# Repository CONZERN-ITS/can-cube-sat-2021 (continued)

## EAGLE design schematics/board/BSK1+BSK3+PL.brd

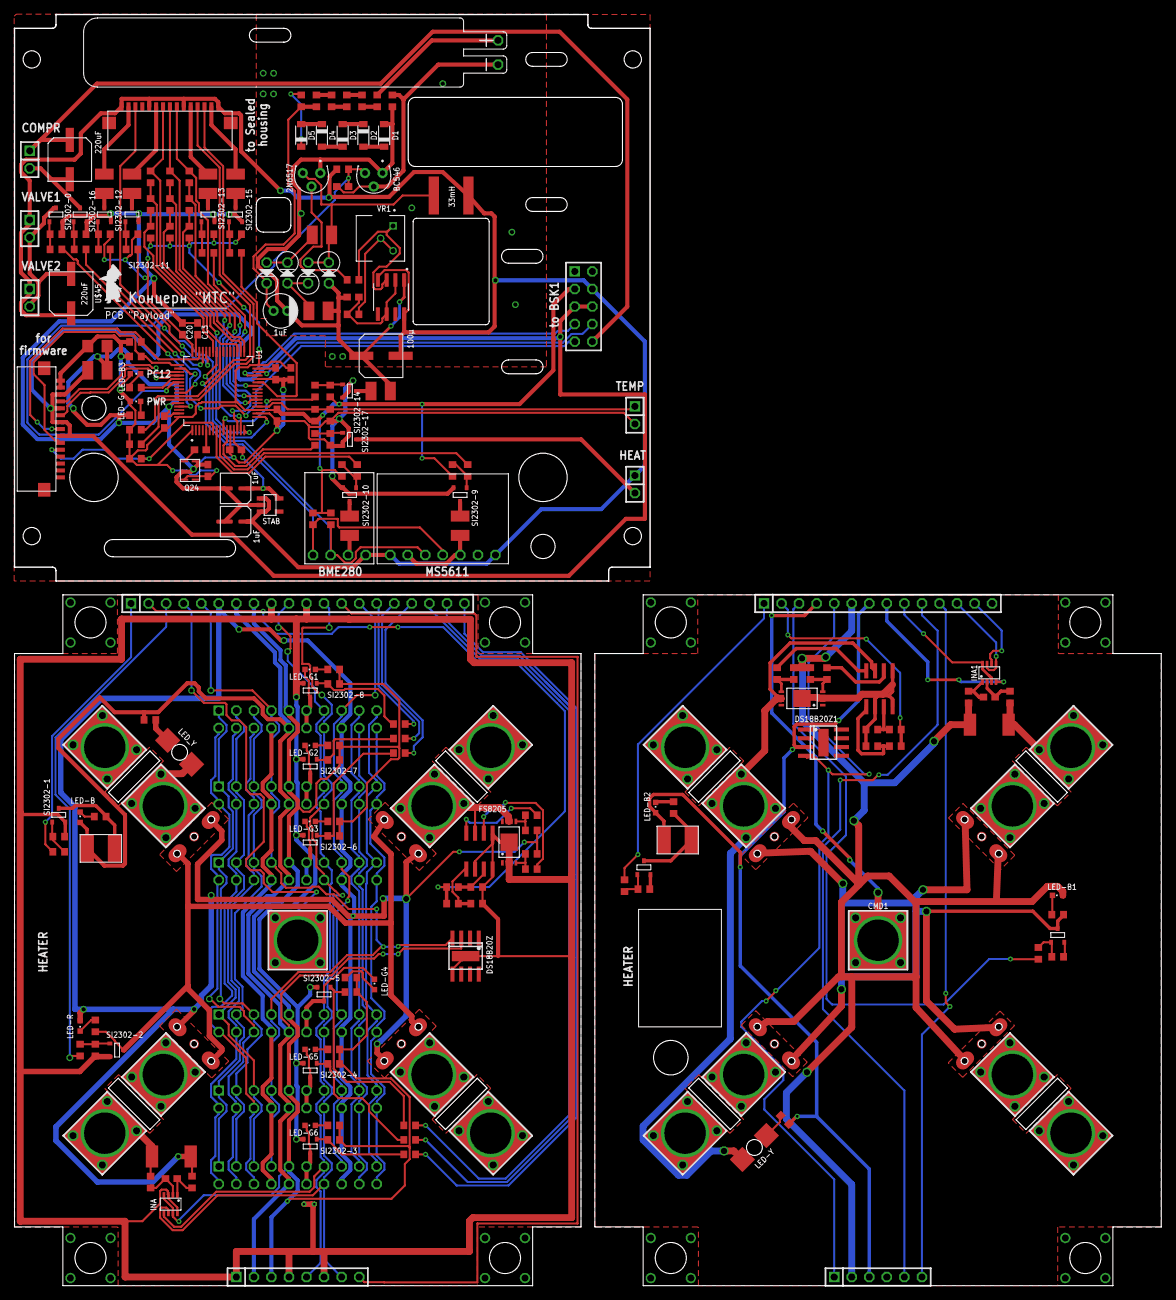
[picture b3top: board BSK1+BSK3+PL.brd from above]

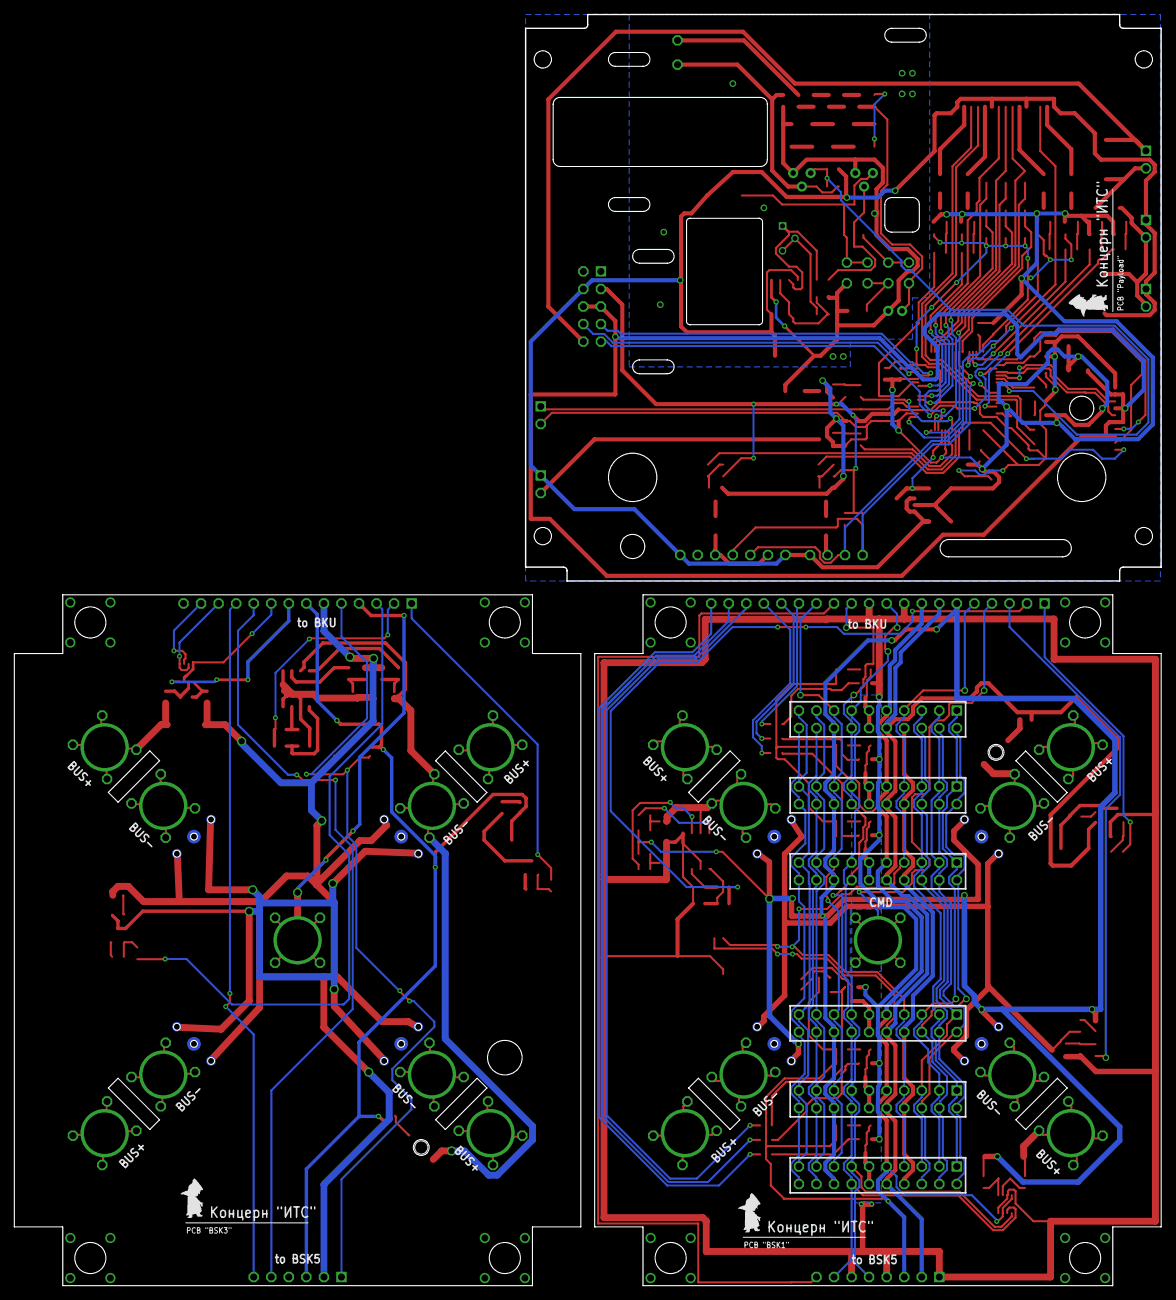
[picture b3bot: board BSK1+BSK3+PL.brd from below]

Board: 2 copper layers, 166.0 x 184.0 mm, 246 parts (9 on the bottom side), 200 nets.

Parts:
2N6517: DS1820; TO92/TO226
BC546: DS1820; TO92/TO226
BKU: 1X20
BKU1: 1X14
BME280: BME280BME280-PINS-ONLY; BME280-PINS-ONLY
BSK1: 1X06
BSK2: 2X05
BSK5: 1X08
C1, C41: 0,1µ; C0603
C2, C3, C4, C6, C18, C20: 100nF; C0603
C5, C7: 22nF; C1210
C8: 1nF; C0603
C9, C13: 2,2µ; C0603
C10: 10nF; C0603
C11: 100pF; C0603
C12, C14: 1uF; ECAP-SMD-D4
C19: 10µ; C1206
CMD, CMD1: KCONNECTQUAD; KCONNECT_QUAD
COMPR: 1X02
D1, D2, D3, D4, D5: DIODE-MBR; SOD123
DS18B20Z, DS18B20Z1: DS18B20Z; SOIC8+HEAT_S
FS8205: FS8205A+
HEAT: 1X02
INA, INA1: INA219AID; SOT23-8
JP1, JP2, JP3, JP4, JP5, JP6: 2X10
LED-B, LED-B1, LED-B2, LED-B3: CHIPLED_0603
LED-G, LED-G1, LED-G2, LED-G3, LED-G4, LED-G5, LED-G6: CHIPLED_0603
LED-R: CHIPLED_0603
LED-Y: LAP4-BOTTOM; P47F-BOTTOM
LED_Y: LAP4-BOTTOM; P47F-BOTTOM
MS5611: MS5611MS5611-PIN-ONLY; MS5611-PINS-ONLY
Q24: Q24
R1, R2, R94, R95: 200k; R0603
R3, R5, R26, R27, R28, R29, R30, R31, R32, R33, R34, R35, R48, R49, R59, R61, R64, R66, R69, R72, R101, R104, R106, R108: 100R; R0603
R4, R7, R36, R37, R87: 100k; R0603
R6, R8, R9, R12, R13, R14, R18, R20, R40, R42, R58, R60, R63, R65, R68, R71, R82, R83, R84, R85, R86, R100, R103, R105, R107: 1M; R0603
R10, R11, R15, R16, R17, R21, R22, R23, R38, R39, R51, R54: 2k; R0603
R19, R88: 3k3; R0603
R24, R25, R46, R47: 2k26; R0603
R41: 1k5; R0603
R43, R75: R01; R2512
R44, R45, R76, R77: 10R; R0603
R50, R52, R53, R89, R90, R91, R92, R93, R96, R97, R98, R99: 10k; R0603
R55, R56, R111, R112: 5k1; R0603
R57, R62, R67, R70, R73, R74, R102: 0.05A; R1210
R78: 0.5A; R1210
R79: 1k; R0603
R80: 4k7; R0603
R81, R110: 22k; R0603
R109: 124k; R0603
SI2302-0, SI2302-1, SI2302-2, SI2302-3, SI2302-4, SI2302-5, SI2302-6, SI2302-7, SI2302-8, SI2302-9, SI2302-10, SI2302-11, SI2302-12, SI2302-13, SI2302-14, SI2302-15, SI2302-16, SI2302-17: SI2302CDS; SOT23-3
STAB: ADP150AUJZ-3.3-R7; SOT23-5
TEMP: 1X02
U1: STM32F405RGT6; QFP50P1200X1200X160-64N
U2: LMC555; SOIC127P599X175-8N
U$1, U$2, U$3, U$4, U$5, U$6, U$7, U$8, U$9, U$10, U$11, U$12, U$18, U$19, U$20, U$21: KCONNECT
U$13: FS8205A+
U$14, U$22: MOCD; SOIC8
U$15, U$17: SI2302CDS; SOT23-3
U$16, U$24: EM_HEAT
U$23, U$25, U$27, U$28, U$29, U$30, U$31, U$32: GRAFITGRAFIT4_2; GRAFIT4_2
U$26: PCB "BSK1"; ITS-LOGO
U$33: PCB "BSK3"; ITS-LOGO
U$34: 100µ; ECAP100-CMD
U$35, U$36, U$37, U$38: BA159
U$39: 1uF; ECAP1MK
U$40: DOSIM
U$41, U$43: FFC-CONNECT68611; 68611
U$42: 33mH; RCH114NP
U$44, U$45: 220uF; ECAP220-CMD
U$46, U$47: PCB "Payload"; ITS-LOGO
VALVE1, VALVE2: 1X02
VR1: 3362H-1-502LF; TRIM_3362H-1-502LF

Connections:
1: R39.2, U$15.3, U$16.2
1W: BKU.5, DS18B20Z.4, JP1.7, JP2.7, JP3.7, JP4.7, JP5.7, JP6.7
1W1: BKU1.5, BSK1.1, DS18B20Z1.4
2: R41.2, U$17.3, U$23.P$1, U$23.P$4, U$25.P$1, U$25.P$4, U$31.P$1, U$31.P$4, U$32.P$1, U$32.P$4
3: R11.2, SI2302-1.3, U$24.2
3V1: BKU1.8, INA1.4
3V2: BSK2.3, C2.2, C6.2, C10.2, C18.2, C19.2, C20.2, LED-B3.A, LED-G.A, Q24.P$4, R50.2, R52.2, R53.2, R55.1, R56.1, R58.2, R60.2, R63.2, R65.2, R68.2, R71.2, R97.2, R98.2, R99.2, R100.2, R110.2, R111.1, R112.1, U1.1, U1.19, U1.32, U1.48, U1.64, U$43.P$1, U$43.P$2
3V3: BKU.8, BSK5.3, INA.4, INA.7, JP1.9, JP2.9, JP3.9, JP4.9, JP5.9, JP6.9, R6.1, R8.2, R9.1, R12.1, R13.2, R14.1, R15.1, R16.1, R17.1, R21.1, R22.1, R23.1
4: R19.2, SI2302-2.3, U$27.P$1, U$27.P$4, U$28.P$1, U$28.P$4, U$29.P$1, U$29.P$4, U$30.P$1, U$30.P$4
4OXV: R66.1, U1.45
5V: BKU.7, BSK5.2, DS18B20Z.3, JP1.10, JP2.10, JP3.10, JP4.10, JP5.10, JP6.10, LED-B.A, R10.1, U$24.1
5V1: BKU1.7, BSK1.3, DS18B20Z1.3, LED-B2.A, R38.1, U$16.1
5V2: BME280.P$1, BSK2.4, C14.P+, HEAT.1, MS5611.P$1, MS5611.P$7, R88.1, STAB.P$1, STAB.P$3, U2.4, U2.8, U$34.P$2, U$41.P$1, U$41.P$5, U$41.P$10, U$41.P$15, U$42.P$1, U$45.P$1, VALVE1.1, VALVE2.1
B1-CMD: BKU.4, CMD.1, CMD.2, CMD.3, CMD.4, CMD.P$1, CMD.P$2
B1-KHEAT: BKU.1, R32.2
B1-KVCC: BKU.2, R24.2, R25.2
B1-ROZE: BKU.3, R33.2
B3-CMD: BKU1.4, CMD1.1, CMD1.2, CMD1.3, CMD1.4, CMD1.P$1, CMD1.P$2
B3-KHEAT: BKU1.1, R48.2
B3-KVCC: BKU1.2, R46.2, R47.2
B3-ROZE: BKU1.3, R49.2
B5-KHEAT: BKU1.10, BSK1.5
BME280-EXT: R61.1, U1.8
BME280-INT: R101.1, U1.27
BMS1: JP1.1, JP2.1, JP3.1, JP4.5, JP5.3, JP6.3
BMS2: JP1.2, JP2.2, JP3.2, JP4.6, JP5.4, JP6.4
BMS3: JP1.3, JP2.3, JP3.3, JP4.1, JP5.5, JP6.5
BMS4: JP1.4, JP2.4, JP3.4, JP4.2, JP5.6, JP6.6
BMS5: JP1.5, JP2.5, JP3.5, JP4.3, JP5.1, JP6.1
BMS6: JP1.6, JP2.6, JP3.6, JP4.4, JP5.2, JP6.2
BMS+: JP1.8, JP2.8, JP3.8, JP4.8, JP5.8, JP6.8
BUS+: BKU.6, JP1.16, JP2.16, JP3.16, JP4.16, JP5.16, JP6.16, LED-R.A, R4.1, R7.2, R75.2, R76.1, U$27.P$2, U$27.P$5, U$28.P$2, U$28.P$5, U$29.P$2, U$29.P$5, U$30.P$2, U$30.P$5
BUS+1: BKU1.6, BSK1.2, LED-B1.A, R36.1, R37.2, R43.2, R44.1, U$23.P$2, U$23.P$5, U$25.P$2, U$25.P$5, U$31.P$2, U$31.P$5, U$32.P$2, U$32.P$5
BUS+2: BSK2.10, COMPR.1, U$44.P$1
CO: R91.1, U1.16, U$41.P$7
COMPR: R106.1, U1.57
CTRL-CO-1: R91.2, R96.1, U1.35
CTRL-CO-2: R96.2, R97.1, U1.42
CTRL-NH3-1: R90.2, R93.1, U1.33
CTRL-NH3-2: R93.2, R98.1, U1.34
CTRL-NO2-1: R89.2, R92.1, U1.23
CTRL-NO2-2: R92.2, R99.1, U1.22
DOS-G: 2N6517.1, BC546.1, C4.1, C7.2, D1.A, R73.1, R87.2, U2.1, U$34.P$1, U$35.P$1, U$39.P$2
DOSE: BC546.3, C11.2, R88.2, U1.54
DOSIM: R72.1, U1.10
G-4OXV: R67.1, U$41.P$2
G-BME: R102.1, U$41.P$14
G-MICS: R74.1, U$41.P$6
G-MS: R70.1, U$41.P$11
GND: BKU.9, BKU.11, BSK5.1, BSK5.4, BSK5.6, DS18B20Z.5, DS18B20Z.HEAT, FS8205.23, FS8205.HEAT, INA.3, INA.8, R1.1, R2.1, R18.2, R20.2, SI2302-1.2, SI2302-2.2, SI2302-3.2, SI2302-4.2, SI2302-5.2, SI2302-6.2, SI2302-7.2, SI2302-8.2, U$22.2, U$22.4, U$22.5
GND4: BKU1.9, BKU1.14, BSK1.4, DS18B20Z1.5, DS18B20Z1.HEAT, INA1.3, INA1.8, R40.2, R42.2, R94.1, R95.1, U$13.23, U$13.HEAT, U$14.2, U$14.4, U$14.5, U$15.2, U$17.2
GND9: C2.1, C3.2, C6.1, C9.1, C10.1, C12.P-, C13.1, C14.P-, C18.1, C19.1, C20.1, Q24.P$2, R54.1, R78.1, R103.2, R105.2, R107.2, R109.1, SI2302-0.2, SI2302-9.2, SI2302-10.2, SI2302-11.2, SI2302-12.2, SI2302-13.2, SI2302-14.2, SI2302-15.2, SI2302-16.2, SI2302-17.2, STAB.P$2, TEMP.2, U1.12, U1.18, U1.28, U1.60, U1.63
GND-4OXV: R67.2, SI2302-12.3
GND-BME-EXT: R62.2, SI2302-10.3
GND-BME-INT: R102.2, SI2302-15.3
GND-COMPR: COMPR.2, SI2302-16.3, U$44.P$2
GND-DOSIM: R73.2, SI2302-14.3
GND-HEAT: HEAT.2, SI2302-17.3
GND-MICS: R74.2, SI2302-11.3
GND-MS-EXT: R57.2, SI2302-9.3
GND-MS-INT: R70.2, SI2302-13.3
GND-OUT: BSK2.5, BSK2.6, R78.2, U$43.P$3, U$43.P$5, U$43.P$7, U$43.P$9
GND-VALVE: SI2302-0.3, U$45.P$2, VALVE1.2, VALVE2.2
HEAT: R108.1, U1.11
MICS: R64.1, U1.44
MS5611-EXT: R59.1, U1.9
MS5611-INT: R69.1, U1.26
unnamed: FS8205.5, R4.2, R5.1
unnamed: LED-B.C, R11.1
unnamed: LED-R.C, R19.1
unnamed: LED-G1.A, R16.2
unnamed: LED-G3.A, R17.2
unnamed: LED-G4.A, R21.2
unnamed: LED-G5.A, R22.2
unnamed: LED-G6.A, R23.2
unnamed: R1.2, R24.1, U$22.1
unnamed: R2.2, R25.1, U$22.3
unnamed: FS8205.4, R3.1, R7.1
unnamed: LED_Y.A, R10.2
unnamed: R13.1, R26.1, SI2302-4.1
unnamed: R9.2, R27.1, SI2302-6.1
unnamed: R6.2, R28.1, SI2302-8.1
unnamed: R14.2, R31.1, SI2302-3.1
unnamed: R35.1, R36.2, U$13.5
unnamed: R8.1, R29.1, SI2302-7.1
unnamed: R12.2, R30.1, SI2302-5.1
unnamed: R18.1, R32.1, SI2302-1.1
unnamed: R20.1, R33.1, SI2302-2.1
unnamed: LED-G2.A, R15.2
unnamed: R34.1, R37.1, U$13.4
unnamed: LED-Y.A, R38.2
unnamed: LED-B2.C, R39.1
unnamed: LED-B1.C, R41.1
unnamed: C1.1, INA1.1, R44.2
unnamed: C1.2, INA1.2, R45.2
unnamed: R46.1, R94.2, U$14.1
unnamed: R47.1, R95.2, U$14.3
unnamed: R40.1, R48.1, U$15.1
unnamed: R42.1, R49.1, U$17.1
unnamed: R51.1, U1.53
unnamed: C13.2, U1.47
unnamed: C9.2, U1.31
unnamed: C8.1, U1.5
unnamed: LED-B3.C, R51.2
unnamed: C8.2, Q24.P$3
unnamed: R58.1, R59.2, SI2302-9.1
unnamed: MS5611.P$3, MS5611.P$6, R57.1
unnamed: R60.1, R61.2, SI2302-10.1
unnamed: BME280.P$2, R62.1
unnamed: R63.1, R64.2, SI2302-11.1
unnamed: R65.1, R66.2, SI2302-12.1
unnamed: R68.1, R69.2, SI2302-13.1
unnamed: R71.1, R72.2, SI2302-14.1
unnamed: C4.2, R79.1, U2.2, U2.6
unnamed: R79.2, VR1.2, VR1.3
unnamed: R80.2, U2.3, VR1.1
unnamed: 2N6517.2, R80.1
unnamed: 2N6517.3, C5.1, U$35.P$2, U$36.P$1, U$42.P$2
unnamed: C7.1, U$36.P$2, U$37.P$1
unnamed: C5.2, U$37.P$2, U$38.P$1
unnamed: R81.2, R82.2, U$38.P$2, U$39.P$1
unnamed: D1.C, D2.A
unnamed: D2.C, D3.A
unnamed: D3.C, D4.A
unnamed: D4.C, D5.A
unnamed: D5.C, R81.1
unnamed: R82.1, R83.1
unnamed: R83.2, R84.2
unnamed: R84.1, R85.1
unnamed: R85.2, R86.2
unnamed: R86.1, U$40.P$1
unnamed: BC546.2, C11.1, R87.1, U$40.P$2
unnamed: R100.1, R101.2, SI2302-15.1
unnamed: R103.1, R104.2, SI2302-0.1
unnamed: R105.1, R106.2, SI2302-16.1
unnamed: R107.1, R108.2, SI2302-17.1
unnamed: C3.1, C12.P+, STAB.P$5, U1.13
unnamed: LED-G.C, R54.2
unnamed: C41.1, INA.1, R76.2
unnamed: C41.2, INA.2, R77.2
NH3: R90.1, U1.15, U$41.P$8
NO2: R89.1, U1.14, U$41.P$9
NRST: R50.1, U1.7, U$43.P$11
O2: U1.17, U$41.P$3
OC1: R34.2, U$14.6
OC2: R3.2, U$22.6
OD1: R35.2, U$14.8
OD2: R5.2, U$22.8
PL1: JP1.17, JP2.17, JP3.17, JP4.17, JP5.17, JP6.17
PL1-GND: JP1.11, JP1.12, LED-G1.C, SI2302-8.3
PL1-KVCC: BKU.15, R28.2
PL2: JP1.18, JP2.18, JP3.18, JP4.18, JP5.18, JP6.18
PL2-GND: JP2.11, JP2.12, LED-G2.C, SI2302-7.3
PL2-KVCC: BKU.16, R29.2
PL3: JP1.19, JP2.19, JP3.19, JP4.19, JP5.19, JP6.19
PL3-GND: JP3.11, JP3.12, LED-G3.C, SI2302-6.3
PL3-KVCC: BKU.17, R27.2
PL4: JP1.20, JP2.20, JP3.20, JP4.20, JP5.20, JP6.20
PL4-GND: JP4.11, JP4.12, LED-G4.C, SI2302-5.3
PL4-KVCC: BKU.18, R30.2
PL5-GND: JP5.11, JP5.12, LED-G5.C, SI2302-4.3
PL5-KVCC: BKU.19, R26.2
PL6-GND: JP6.11, JP6.12, LED-G6.C, SI2302-3.3
PL6-KVCC: BKU.20, R31.2
RX-S: U1.52, U$43.P$4
SCL-TM: BKU.10, BSK5.5, INA.5, JP1.13, JP2.13, JP3.13, JP4.13, JP5.13, JP6.13
SCL-TM1: BKU1.12, INA1.5, INA1.7
SCL-TM2: BSK2.7, U1.29
SDA-TM: BKU.12, BSK5.7, INA.6, JP1.14, JP2.14, JP3.14, JP4.14, JP5.14, JP6.14
SDA-TM1: BKU1.13, INA1.6
SDA-TM2: BSK2.8, U1.30
SENS-EXT-SCL: BME280.P$3, MS5611.P$5, R112.2, U1.41
SENS-EXT-SDA: BME280.P$4, MS5611.P$4, R111.2, U1.40
SENS-INT-SCL: R55.2, U1.58, U$41.P$12
SENS-INT-SDA: R56.2, U1.59, U$41.P$13
SINS-KVCC: BKU1.11, BSK1.6
SP+: U$20.1, U$20.2, U$20.3, U$20.4, U$20.P$1, U$20.P$2
SP+1: U$1.1, U$1.2, U$1.3, U$1.4, U$1.P$1, U$1.P$2
SP+2: U$3.1, U$3.2, U$3.3, U$3.4, U$3.P$1, U$3.P$2
SP+3: R75.1, R77.1, U$18.1, U$18.2, U$18.3, U$18.4, U$18.P$1, U$18.P$2
SP+4: U$5.1, U$5.2, U$5.3, U$5.4, U$5.P$1, U$5.P$2
SP+5: U$6.1, U$6.2, U$6.3, U$6.4, U$6.P$1, U$6.P$2
SP+6: U$9.1, U$9.2, U$9.3, U$9.4, U$9.P$1, U$9.P$2
SP+7: R43.1, R45.1, U$11.1, U$11.2, U$11.3, U$11.4, U$11.P$1, U$11.P$2
SP-: LED_Y.C, U$2.1, U$2.2, U$2.3, U$2.4, U$2.P$1, U$2.P$2
SP-1: FS8205.67, U$4.1, U$4.2, U$4.3, U$4.4, U$4.P$1, U$4.P$2, U$22.7
SP-2: U$19.1, U$19.2, U$19.3, U$19.4, U$19.P$1, U$19.P$2
SP-3: U$21.1, U$21.2, U$21.3, U$21.4, U$21.P$1, U$21.P$2
SP-4: U$12.1, U$12.2, U$12.3, U$12.4, U$12.P$1, U$12.P$2
SP-5: U$7.1, U$7.2, U$7.3, U$7.4, U$7.P$1, U$7.P$2
SP-6: U$10.1, U$10.2, U$10.3, U$10.4, U$10.P$1, U$10.P$2
SP-7: LED-Y.C, U$8.1, U$8.2, U$8.3, U$8.4, U$8.P$1, U$8.P$2, U$13.67, U$14.7
SWC: R53.1, U1.49, U$43.P$10
SWD: R52.1, U1.46, U$43.P$8
TEMP: R109.2, R110.1, TEMP.1, U1.20
TIME: BKU.14, JP1.15, JP2.15, JP3.15, JP4.15, JP5.15, JP6.15
TIME1: BSK2.9, U1.50
TIME-ES: BKU.13, BSK5.8
TX-S: U1.51, U$43.P$6
VALVE: R104.1, U1.61

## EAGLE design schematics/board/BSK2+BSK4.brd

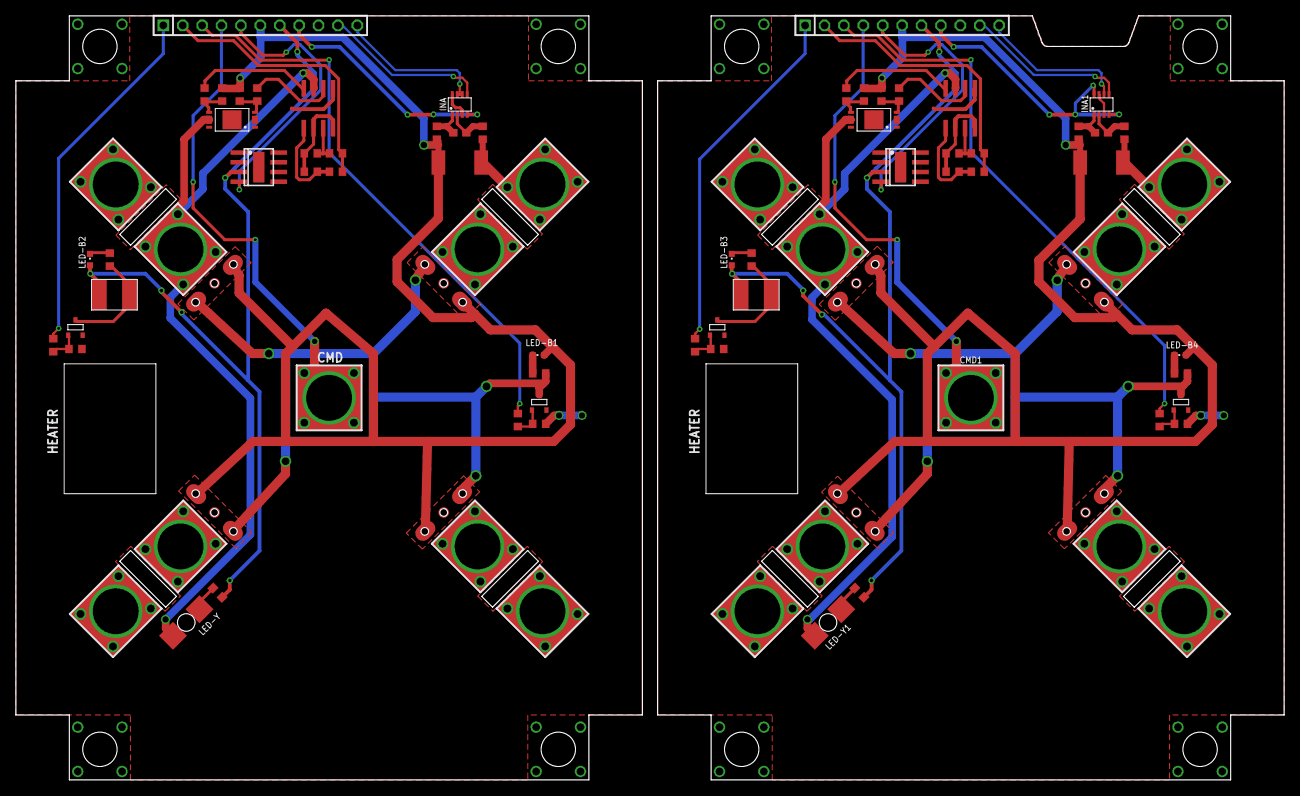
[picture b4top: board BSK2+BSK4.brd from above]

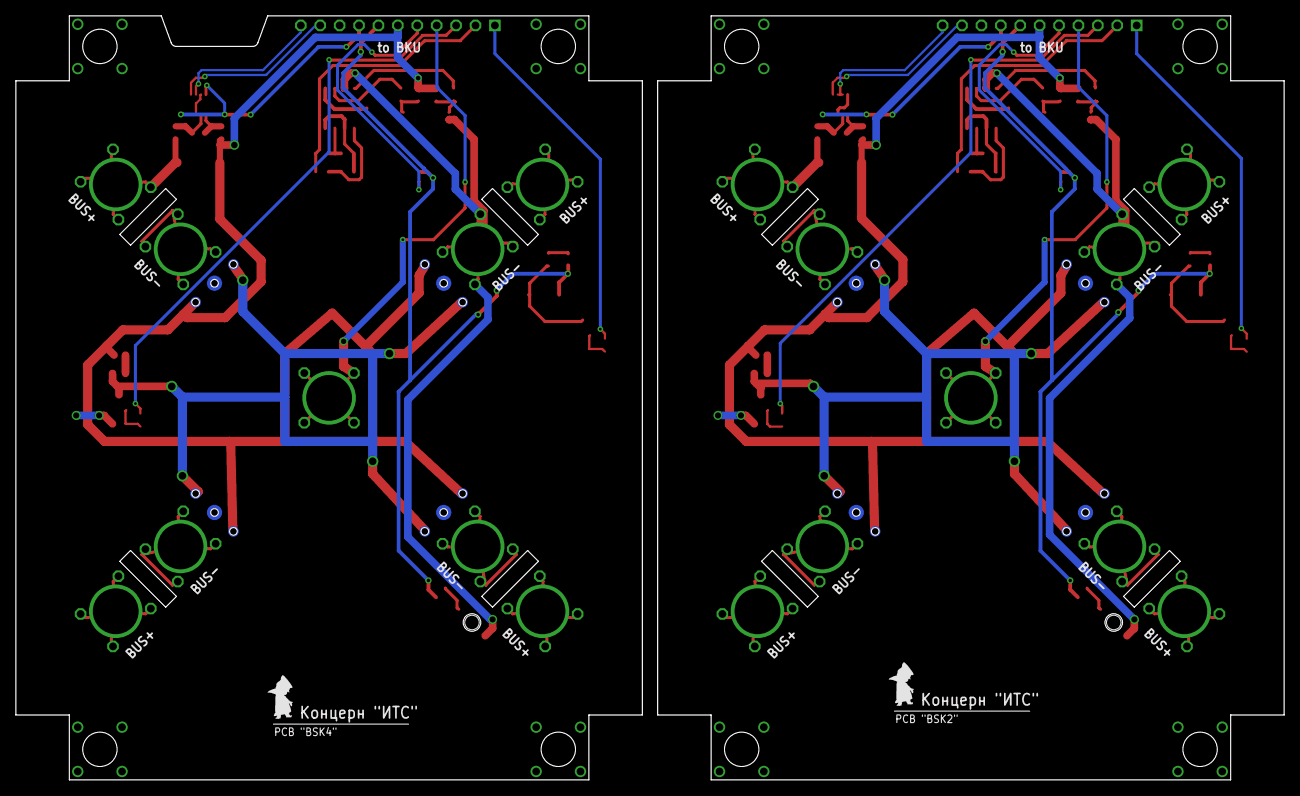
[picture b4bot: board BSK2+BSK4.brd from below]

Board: 2 copper layers, 166.0 x 100.0 mm, 88 parts (2 on the bottom side), 68 nets.

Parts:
BKU, BKU1: 1X11
C1, C41: 0,1µ; C0603
CMD, CMD1: KCONNECTQUAD; KCONNECT_QUAD
DS18B20Z1, DS18B20Z2: DS18B20Z; SOIC8+HEAT_S
INA, INA1: INA219AID; SOT23-8
LED-B1, LED-B2, LED-B3, LED-B4: CHIPLED_0603
LED-Y, LED-Y1: LAP4-BOTTOM; P47F-BOTTOM
MOCD: MOCD; SOIC8
R1, R2, R27, R28: 2k26; R0603
R3, R5, R9, R15, R16, R29, R30, R32: 100R; R0603
R4, R7, R19, R20: 2k; R0603
R6, R12, R17, R18: 100k; R0603
R8, R14, R21, R23: 1M; R0603
R10, R11, R94, R95: 200k; R0603
R13, R22: 3k3; R0603
R24, R75: R01; R2512
R25, R26, R76, R77: 10R; R0603
U$1, U$2, U$3, U$4, U$5, U$9, U$10, U$11, U$12, U$18, U$19, U$20, U$21, U$22, U$23, U$24: KCONNECT
U$6, U$7, U$15, U$16, U$31, U$32, U$33, U$34: GRAFITGRAFIT4_2; GRAFIT4_2
U$8, U$13, U$28, U$30: SI2302CDS; SOT23-3
U$14, U$29: EM_HEAT
U$17: PCB "BSK2"; ITS-LOGO
U$25, U$26: FS8205A+
U$27: MOCD; SOIC8
U$35: PCB "BSK4"; ITS-LOGO

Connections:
1: R7.2, U$8.3, U$14.2
1W: BKU.5, DS18B20Z1.4
1W1: BKU1.5, DS18B20Z2.4
2: R13.2, U$6.P$1, U$6.P$4, U$7.P$1, U$7.P$4, U$13.3, U$15.P$1, U$15.P$4, U$16.P$1, U$16.P$4
3: R20.2, U$28.3, U$29.2
3V1: BKU1.8, INA1.4, INA1.8
3V3: BKU.8, INA.4
4: R22.2, U$30.3, U$31.P$1, U$31.P$4, U$32.P$1, U$32.P$4, U$33.P$1, U$33.P$4, U$34.P$1, U$34.P$4
5V: BKU.7, DS18B20Z1.3, LED-B2.A, R4.1, U$14.1
5V1: BKU1.7, DS18B20Z2.3, LED-B3.A, R19.1, U$29.1
B2-CMD: BKU.4, CMD.1, CMD.2, CMD.3, CMD.4, CMD.P$1, CMD.P$2
B2-KHEAT: BKU.1, R32.2
B2-KVCC: BKU.2, R1.2, R2.2
B2-ROZE: BKU.3, R3.2
B4-CMD: BKU1.4, CMD1.1, CMD1.2, CMD1.3, CMD1.4, CMD1.P$1, CMD1.P$2
B4-KHEAT: BKU1.1, R29.2
B4-KVCC: BKU1.2, R27.2, R28.2
B4-ROZE: BKU1.3, R30.2
BUS+: BKU.6, LED-B1.A, R6.1, R12.2, R75.2, R76.1, U$6.P$2, U$6.P$5, U$7.P$2, U$7.P$5, U$15.P$2, U$15.P$5, U$16.P$2, U$16.P$5
BUS+1: BKU1.6, LED-B4.A, R17.1, R18.2, R24.2, R25.1, U$31.P$2, U$31.P$5, U$32.P$2, U$32.P$5, U$33.P$2, U$33.P$5, U$34.P$2, U$34.P$5
GND: BKU.9, DS18B20Z1.5, DS18B20Z1.HEAT, INA.3, INA.8, MOCD.2, MOCD.4, MOCD.5, R8.2, R14.2, R94.1, R95.1, U$8.2, U$13.2, U$26.23, U$26.HEAT
GND4: BKU1.9, DS18B20Z2.5, DS18B20Z2.HEAT, INA1.3, INA1.7, R10.1, R11.1, R21.2, R23.2, U$25.23, U$25.HEAT, U$27.2, U$27.4, U$27.5, U$28.2, U$30.2
unnamed: MOCD.1, R1.1, R94.2
unnamed: MOCD.3, R2.1, R95.2
unnamed: R8.1, R32.1, U$8.1
unnamed: R3.1, R14.1, U$13.1
unnamed: R16.1, R17.2, U$25.5
unnamed: R15.1, R18.1, U$25.4
unnamed: LED-Y1.A, R19.2
unnamed: LED-B3.C, R20.1
unnamed: LED-B4.C, R22.1
unnamed: R5.1, R6.2, U$26.5
unnamed: R9.1, R12.1, U$26.4
unnamed: LED-Y.A, R4.2
unnamed: LED-B1.C, R13.1
unnamed: LED-B2.C, R7.1
unnamed: C1.1, INA1.1, R25.2
unnamed: C1.2, INA1.2, R26.2
unnamed: R10.2, R27.1, U$27.1
unnamed: R11.2, R28.1, U$27.3
unnamed: R21.1, R29.1, U$28.1
unnamed: R23.1, R30.1, U$30.1
unnamed: C41.1, INA.1, R76.2
unnamed: C41.2, INA.2, R77.2
OC1: MOCD.6, R9.2
OC2: R15.2, U$27.6
OD1: MOCD.8, R5.2
OD2: R16.2, U$27.8
SCL-TM: BKU.10, INA.5
SCL-TM1: BKU1.10, INA1.5
SDA-TM: BKU.11, INA.6, INA.7
SDA-TM1: BKU1.11, INA1.6
SP+: R75.1, R77.1, U$3.1, U$3.2, U$3.3, U$3.4, U$3.P$1, U$3.P$2
SP+1: U$1.1, U$1.2, U$1.3, U$1.4, U$1.P$1, U$1.P$2
SP+2: U$9.1, U$9.2, U$9.3, U$9.4, U$9.P$1, U$9.P$2
SP+3: U$11.1, U$11.2, U$11.3, U$11.4, U$11.P$1, U$11.P$2
SP+4: U$5.1, U$5.2, U$5.3, U$5.4, U$5.P$1, U$5.P$2
SP+5: U$24.1, U$24.2, U$24.3, U$24.4, U$24.P$1, U$24.P$2
SP+6: U$19.1, U$19.2, U$19.3, U$19.4, U$19.P$1, U$19.P$2
SP+7: R24.1, R26.1, U$22.1, U$22.2, U$22.3, U$22.4, U$22.P$1, U$22.P$2
SP-: LED-Y.C, MOCD.7, U$2.1, U$2.2, U$2.3, U$2.4, U$2.P$1, U$2.P$2, U$26.67
SP-1: U$4.1, U$4.2, U$4.3, U$4.4, U$4.P$1, U$4.P$2
SP-2: U$10.1, U$10.2, U$10.3, U$10.4, U$10.P$1, U$10.P$2
SP-3: U$12.1, U$12.2, U$12.3, U$12.4, U$12.P$1, U$12.P$2
SP-4: U$23.1, U$23.2, U$23.3, U$23.4, U$23.P$1, U$23.P$2
SP-5: U$18.1, U$18.2, U$18.3, U$18.4, U$18.P$1, U$18.P$2
SP-6: U$20.1, U$20.2, U$20.3, U$20.4, U$20.P$1, U$20.P$2
SP-7: LED-Y1.C, U$21.1, U$21.2, U$21.3, U$21.4, U$21.P$1, U$21.P$2, U$25.67, U$27.7
